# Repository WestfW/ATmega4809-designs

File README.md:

# ATmega4809-designs
A couple of PCB designs using the Microchip ATmega4809 microcontroller.  More-or-less compatible with Arduino

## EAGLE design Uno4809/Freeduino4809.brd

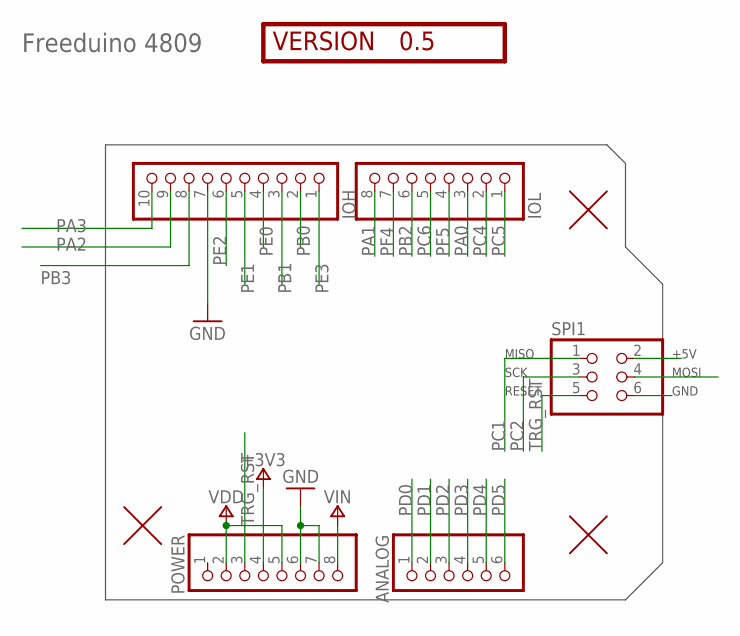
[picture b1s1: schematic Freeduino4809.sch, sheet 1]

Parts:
ANALOG: Analog; 1X06-TH
IOH: Digital; 1X10
IOL: Digital; 1X08
POWER: Power; 1X08
SPI1: -; 2X03
U$1, U$2, U$3: FIDUCIAL1.5X3; FIDUCIAL-1.5X3
VERSION: 0.5; VERSION-NUMBER

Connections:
+3V3: POWER.4; also elsewhere on the board
GND: IOH.7, POWER.6, POWER.7, SPI1.6; also elsewhere on the board
PA0: IOL.3; also elsewhere on the board
PA1: IOL.8; also elsewhere on the board
PA2: IOH.9; also elsewhere on the board
PA3: IOH.10; also elsewhere on the board
PB0: IOH.2; also elsewhere on the board
PB1: IOH.3; also elsewhere on the board
PB2: IOL.6; also elsewhere on the board
PB3: IOH.8; also elsewhere on the board
PC0: SPI1.4; also elsewhere on the board
PC1: SPI1.1; also elsewhere on the board
PC2: SPI1.3; also elsewhere on the board
PC4: IOL.2; also elsewhere on the board
PC5: IOL.1; also elsewhere on the board
PC6: IOL.5; also elsewhere on the board
PD0: ANALOG.1; also elsewhere on the board
PD1: ANALOG.2; also elsewhere on the board
PD2: ANALOG.3; also elsewhere on the board
PD3: ANALOG.4; also elsewhere on the board
PD4: ANALOG.5; also elsewhere on the board
PD5: ANALOG.6; also elsewhere on the board
PE0: IOH.4; also elsewhere on the board
PE1: IOH.5; also elsewhere on the board
PE2: IOH.6; also elsewhere on the board
PE3: IOH.1; also elsewhere on the board
PF4: IOL.7; also elsewhere on the board
PF5: IOL.4; also elsewhere on the board
TRG_RST: POWER.3, SPI1.5; also elsewhere on the board
VDD: POWER.2, POWER.5, SPI1.2; also elsewhere on the board
VIN_EXT: POWER.8; also elsewhere on the board

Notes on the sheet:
Freeduino 4809

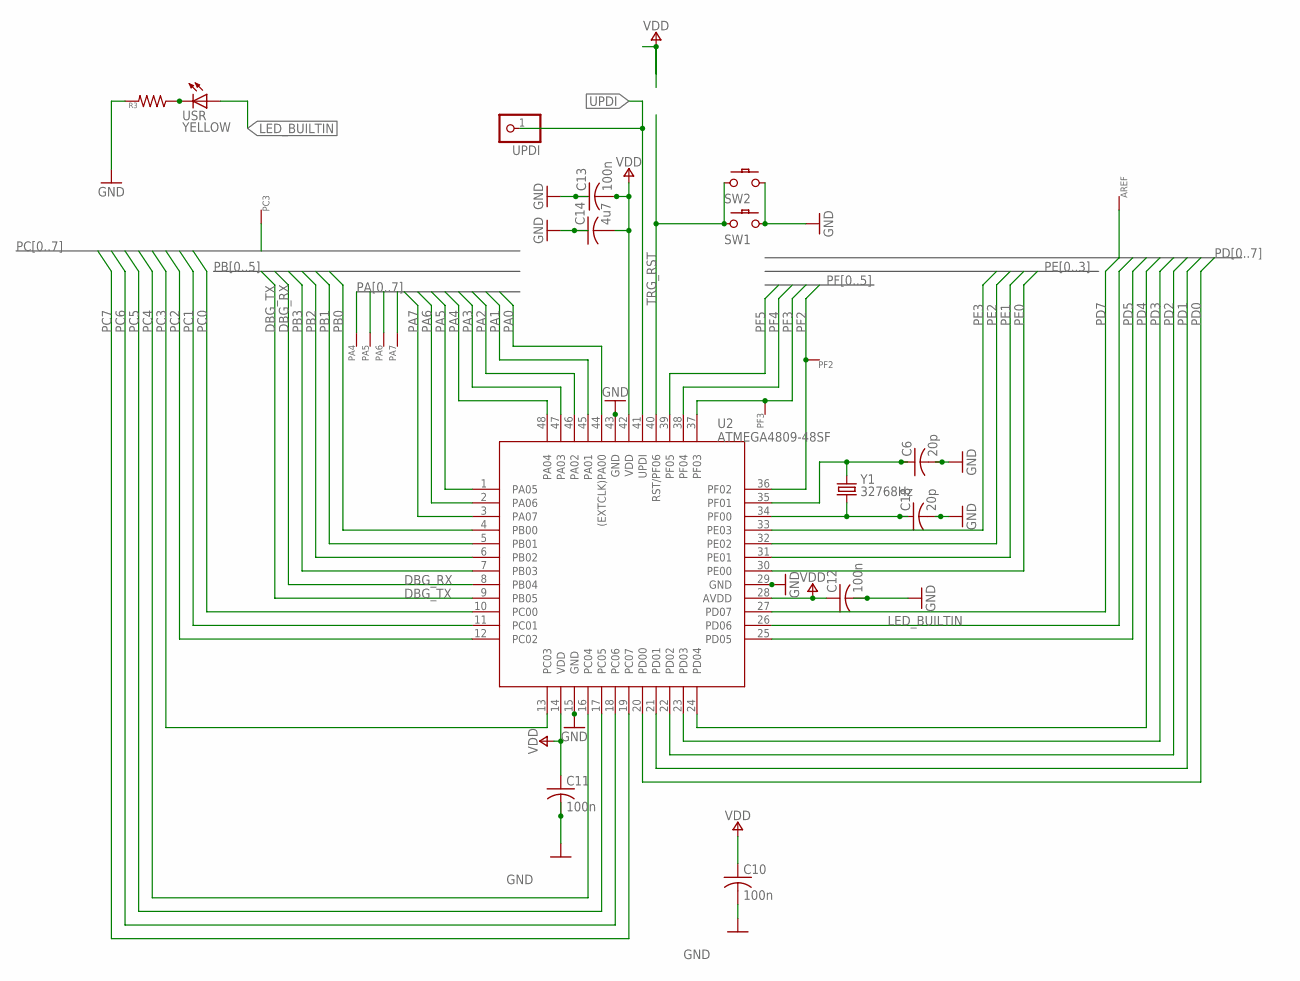
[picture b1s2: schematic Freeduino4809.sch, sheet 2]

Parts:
AREF: WIRE-R10; VIA10
C6, C18: 20p; C0805
C10, C11, C12, C13: 100n; C0805
C14: 4u7; C0805
PA4, PA5, PA6, PA7: WIRE-R6; VIA6
PC3: WIRE-R6; VIA6
PF2, PF3: WIRE-R6; VIA6
R3: R-US_R0805; R0805
SW1: SW-PB2-NS/4MM; SW-PB-SMT4MM
SW2: SW-PB2-NSS52MM\; SW-PB-SMT52MM
U2: ATMEGA4809-48SF; LQFP48-SPARKFUN
UPDI: PINHD-1X1; 1X01
USR: YELLOW; CHIPLED_0805
Y1: 32768Hz; ABS07

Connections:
DBG_RX: U2.8 (PB04); also elsewhere on the board
DBG_TX: U2.9 (PB05); also elsewhere on the board
GND: C6.2, C10.2, C11.2, C12.2, C13.1, C14.1, C18.2, R3.2, SW1.P$4, SW2.S1, U2.15 (GND), U2.29 (GND), U2.43 (GND); also elsewhere on the board
LED_BUILTIN: U2.26 (PD06), USR.A
unnamed: C18.1, U2.34 (PF00), Y1.1
unnamed: C6.1, U2.35 (PF01), Y1.2
unnamed: R3.1, USR.C
PA0: U2.44 ((EXTCLK)PA00); also elsewhere on the board
PA1: U2.45 (PA01); also elsewhere on the board
PA2: U2.46 (PA02); also elsewhere on the board
PA3: U2.47 (PA03); also elsewhere on the board
PA4: PA4.P$1, U2.48 (PA04)
PA5: PA5.P$1, U2.1 (PA05)
PA6: PA6.P$1, U2.2 (PA06)
PA7: PA7.P$1, U2.3 (PA07)
PB0: U2.4 (PB00); also elsewhere on the board
PB1: U2.5 (PB01); also elsewhere on the board
PB2: U2.6 (PB02); also elsewhere on the board
PB3: U2.7 (PB03); also elsewhere on the board
PC0: U2.10 (PC00); also elsewhere on the board
PC1: U2.11 (PC01); also elsewhere on the board
PC2: U2.12 (PC02); also elsewhere on the board
PC3: PC3.P$1, U2.13 (PC03)
PC4: U2.16 (PC04); also elsewhere on the board
PC5: U2.17 (PC05); also elsewhere on the board
PC6: U2.18 (PC06); also elsewhere on the board
PC7: U2.19 (PC07)
PD0: U2.20 (PD00); also elsewhere on the board
PD1: U2.21 (PD01); also elsewhere on the board
PD2: U2.22 (PD02); also elsewhere on the board
PD3: U2.23 (PD03); also elsewhere on the board
PD4: U2.24 (PD04); also elsewhere on the board
PD5: U2.25 (PD05); also elsewhere on the board
PD7: AREF.P$1, U2.27 (PD07)
PE0: U2.30 (PE00); also elsewhere on the board
PE1: U2.31 (PE01); also elsewhere on the board
PE2: U2.32 (PE02); also elsewhere on the board
PE3: U2.33 (PE03); also elsewhere on the board
PF2: PF2.P$1, U2.36 (PF02)
PF3: PF3.P$1, U2.37 (PF03)
PF4: U2.38 (PF04); also elsewhere on the board
PF5: U2.39 (PF05); also elsewhere on the board
TRG_RST: SW1.P$2, SW2.C2, U2.40 (RST/PF06); also elsewhere on the board
UPDI: U2.41 (UPDI), UPDI.1
VDD: C10.1, C11.1, C12.1, C13.2, C14.2, U2.14 (VDD), U2.28 (AVDD), U2.42 (VDD); also elsewhere on the board

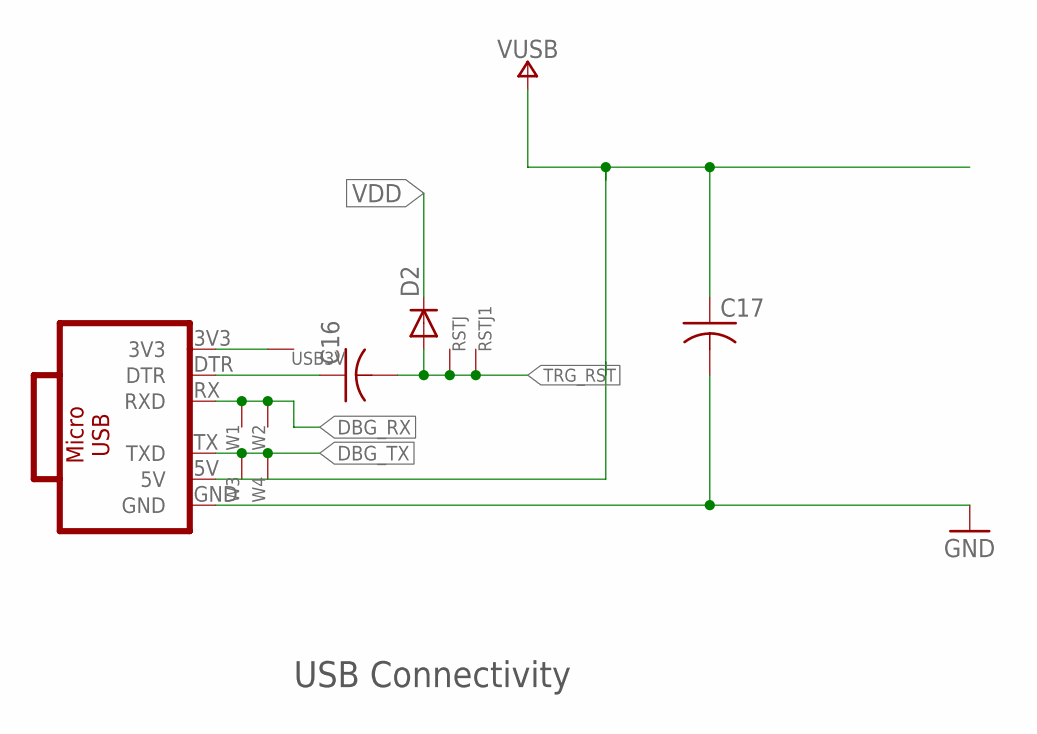
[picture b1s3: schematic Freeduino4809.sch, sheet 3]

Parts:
C16, C17: C-USC0805; C0805
D2: DIODE-SIGNAL-SOD323; SOD323F
RSTJ, RSTJ1: WIRE-R6; VIA6
USB3V: WIRE-VIA8; VIA8
USBMOD: CH340E-MODNOHOLES; CH340E-MOD-NOHOLES
W1, W2, W3, W4: WIRE-R6; VIA6

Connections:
DBG_RX: USBMOD.RX (RXD), W1.P$1, W2.P$1; also elsewhere on the board
DBG_TX: USBMOD.TX (TXD), W3.P$1, W4.P$1; also elsewhere on the board
DTR: C16.1, USBMOD.DTR
GND: C17.2, USBMOD.GND; also elsewhere on the board
TRG_RST: C16.2, D2.A, RSTJ.P$1, RSTJ1.P$1; also elsewhere on the board
USB3V: USB3V.P$1, USBMOD.3V3
VDD: D2.C; also elsewhere on the board
VUSB: C17.1, USBMOD.5V; also elsewhere on the board

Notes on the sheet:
USB Connectivity

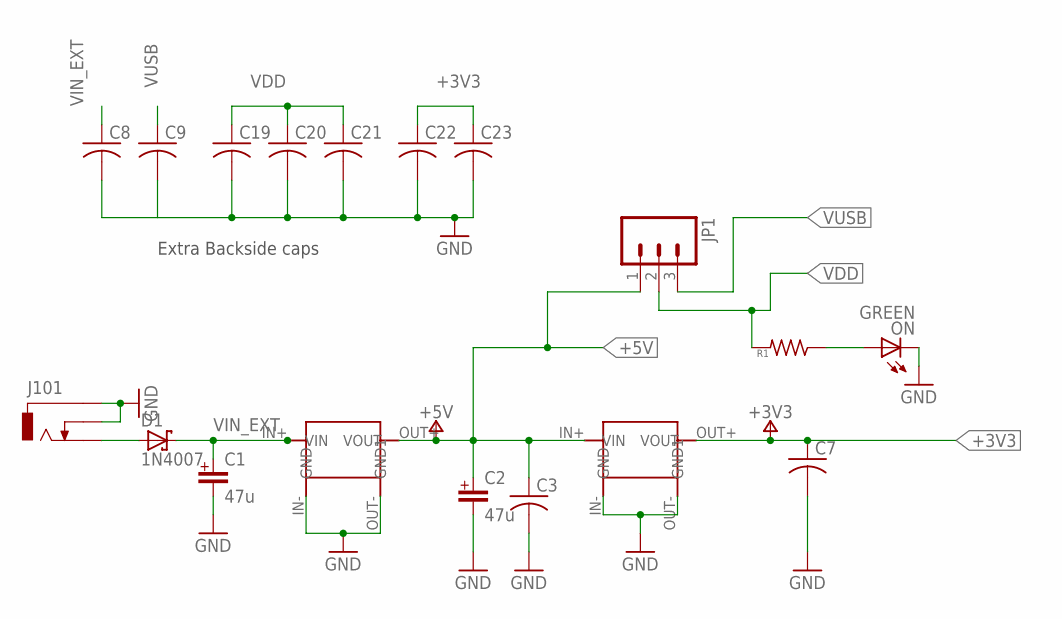
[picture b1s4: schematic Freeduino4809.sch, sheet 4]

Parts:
C1, C2: 47u; PANASONIC_D
C3, C7, C8, C9, C21, C23: C-USC0805; C0805
C19, C20, C22: C-USC1206; C1206
D1: 1N4007; SMB_DO214AA
J101: -; POWERSUPPLY_DC-21MM
JP1: M03LOCK_LONGPADS; 1X03_LOCK_LONGPADS
ON: GREEN; CHIPLED_0805
R1: R-US_R0805; R0805
VREG-3V3, VREG-5V: VREG-4-MOD; VREG-4-11X17

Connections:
+3V3: C7.1, C22.1, C23.1, VREG-3V3.OUT+ (VOUT); also elsewhere on the board
+5V: C2.+, C3.1, JP1.1, VREG-3V3.IN+ (VIN), VREG-5V.OUT+ (VOUT)
GND: C1.-, C2.-, C3.2, C7.2, C8.2, C9.2, C19.2, C20.2, C21.2, C22.2, C23.2, J101.-1 (1), J101.-2 (1), J101.-3 (1), J101.E1 (2), J101.E2 (2), J101.E3 (2), ON.C, VREG-3V3.IN- (GND), VREG-3V3.OUT- (GND1), VREG-5V.IN- (GND), VREG-5V.OUT- (GND1); also elsewhere on the board
unnamed: D1.A, J101.+1 (3), J101.+2 (3), J101.+3 (3)
unnamed: ON.A, R1.1
VDD: C19.1, C20.1, C21.1, JP1.2, R1.2; also elsewhere on the board
VIN_EXT: C1.+, C8.1, D1.C, VREG-5V.IN+ (VIN); also elsewhere on the board
VUSB: C9.1, JP1.3; also elsewhere on the board

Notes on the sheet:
Extra Backside caps

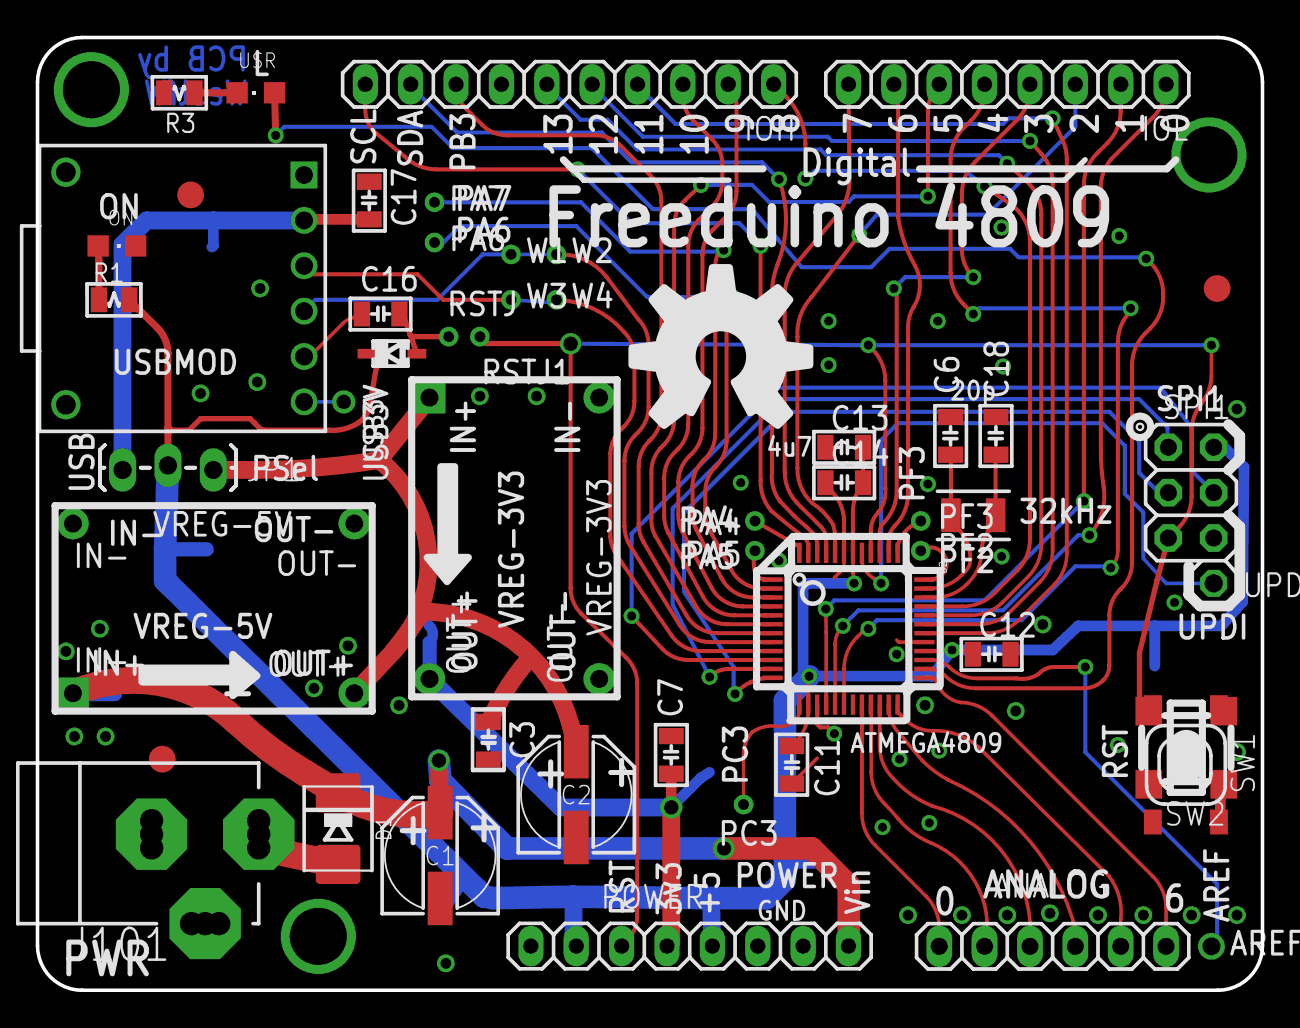
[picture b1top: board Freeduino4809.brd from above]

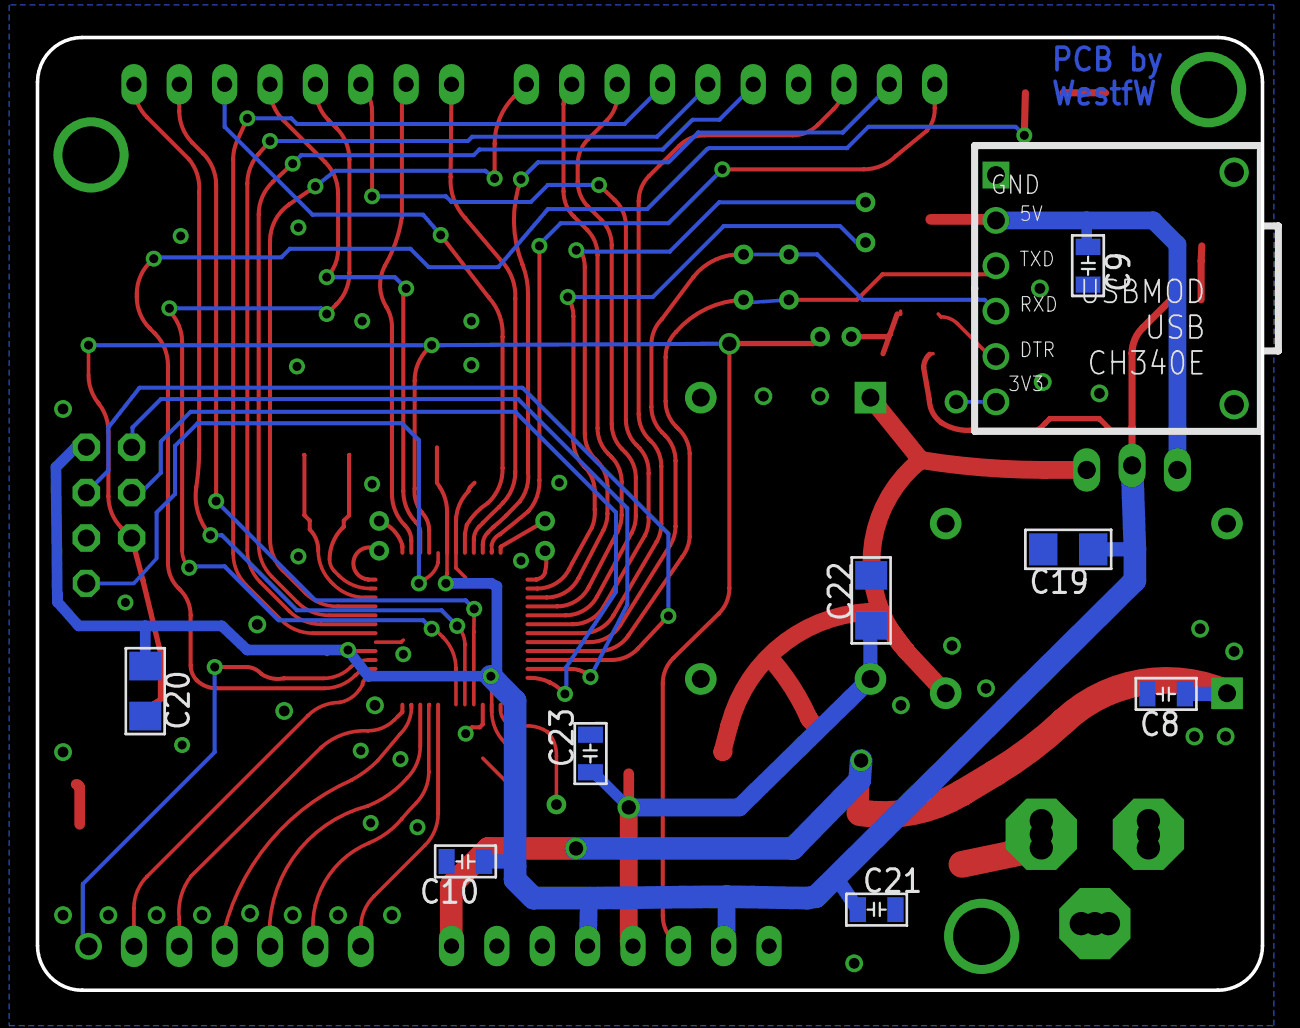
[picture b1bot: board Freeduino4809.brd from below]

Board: 2 copper layers, 68.6 x 53.3 mm, 60 parts (9 on the bottom side), 52 nets.

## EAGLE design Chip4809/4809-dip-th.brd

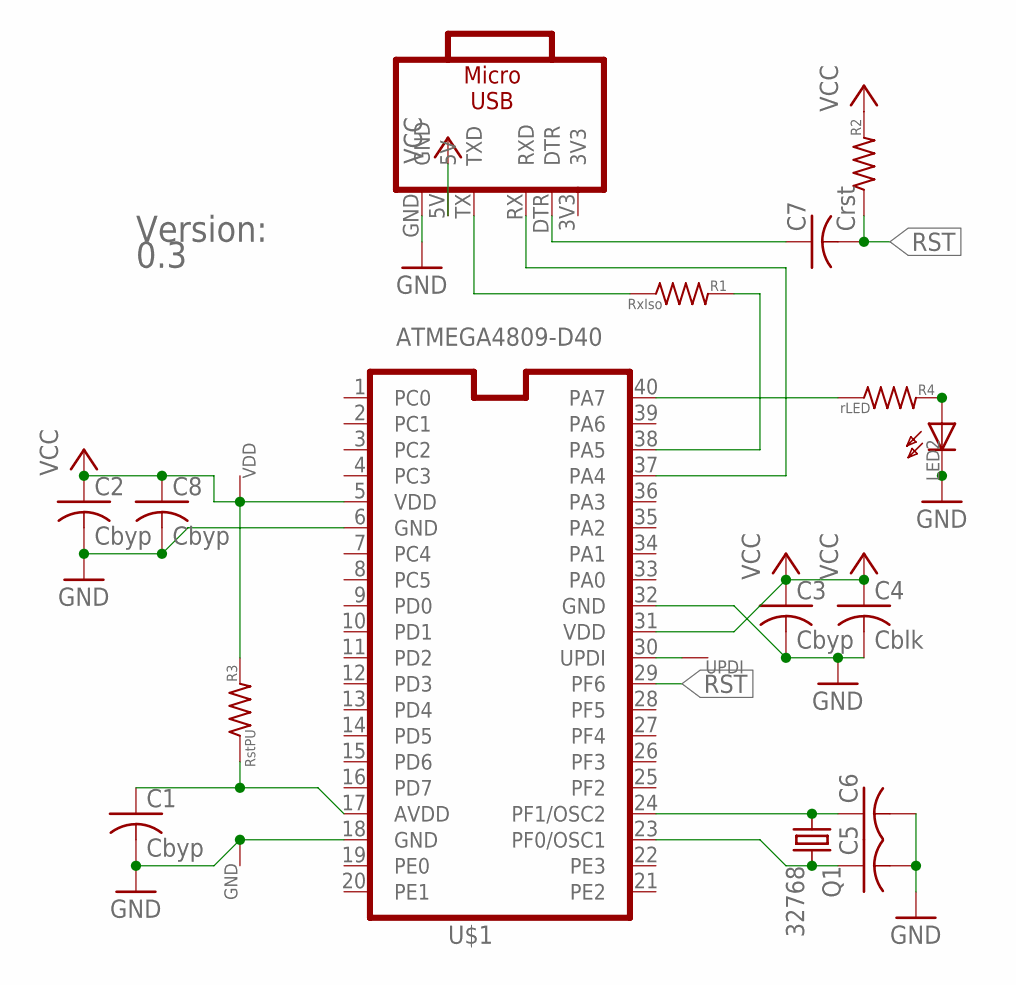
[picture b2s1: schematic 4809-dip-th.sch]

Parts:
C1, C2, C3: Cbyp; C025-025X050
C4: Cblk; C025-025X050
C5, C6: C-US-2.5MM; C025-025X050
C7: Crst; C025-025X050
C8: Cbyp; C1206
GND: WIRE-R10; VIA10
LED2: LED3MM; LED3-2S
MOD1: CH340E-MODNOHOLES; CH340E-MOD-NOHOLES
Q1: 32768; TC26HL
R1: RxIso; 0204/7
R2: R-US_0204/7; 0204/7
R3: RstPU; R0805
R4: rLED; 0204/7
U$1: ATMEGA4809-D40; DIL40SOC
UPDI: WIRE-R10; VIA10
VDD: WIRE-VIA8; VIA8
VS1: 0.3; VERSIONSTRING

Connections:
3V3: MOD1.3V3
GND: C1.2, C2.2, C3.2, C4.2, C5.2, C6.2, C8.2, GND.P$1, LED2.P$2 (C), MOD1.GND, U$1.6 (GND), U$1.18 (GND), U$1.32 (GND)
unnamed: LED2.P$1 (A), R4.2
unnamed: R4.1, U$1.40 (PA7)
unnamed: R1.2, U$1.38 (PA5)
unnamed: MOD1.RX (RXD), U$1.37 (PA4)
unnamed: C1.1, R3.1, U$1.17 (AVDD)
unnamed: C6.1, Q1.1, U$1.24 (PF1/OSC2)
unnamed: C5.1, Q1.2, U$1.23 (PF0/OSC1)
unnamed: C7.1, MOD1.DTR
RST: C7.2, R2.1, U$1.29 (PF6)
UPDI: U$1.30 (UPDI), UPDI.P$1
USBTX: MOD1.TX (TXD), R1.1
VCC: C2.1, C3.1, C4.1, C8.1, MOD1.5V, R2.2, R3.2, U$1.5 (VDD), U$1.31 (VDD), VDD.P$1

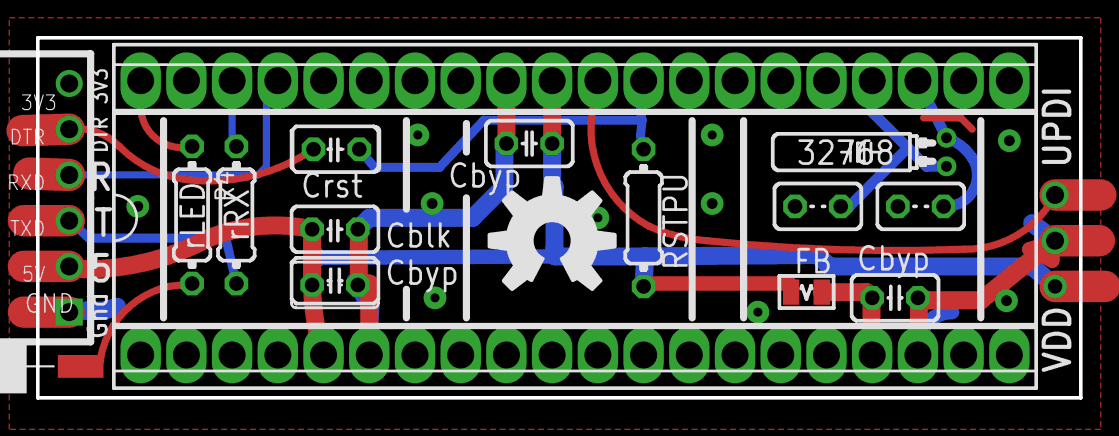
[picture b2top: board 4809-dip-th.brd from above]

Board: 2 copper layers, 57.9 x 20.0 mm, 20 parts (1 on the bottom side), 13 nets.

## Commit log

2019-06-25 Initial checkin.
2020-09-03 Version 0.4 fix RX/TX, move UPDI pin

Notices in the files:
Chip4809/4809-dip-th.brd:
Copyright 2019 by William Westfield
parts and their libraries:
Arduino-connectors: Copyright (c) 2016-2017 Arduino LLC.  All right reserved.
